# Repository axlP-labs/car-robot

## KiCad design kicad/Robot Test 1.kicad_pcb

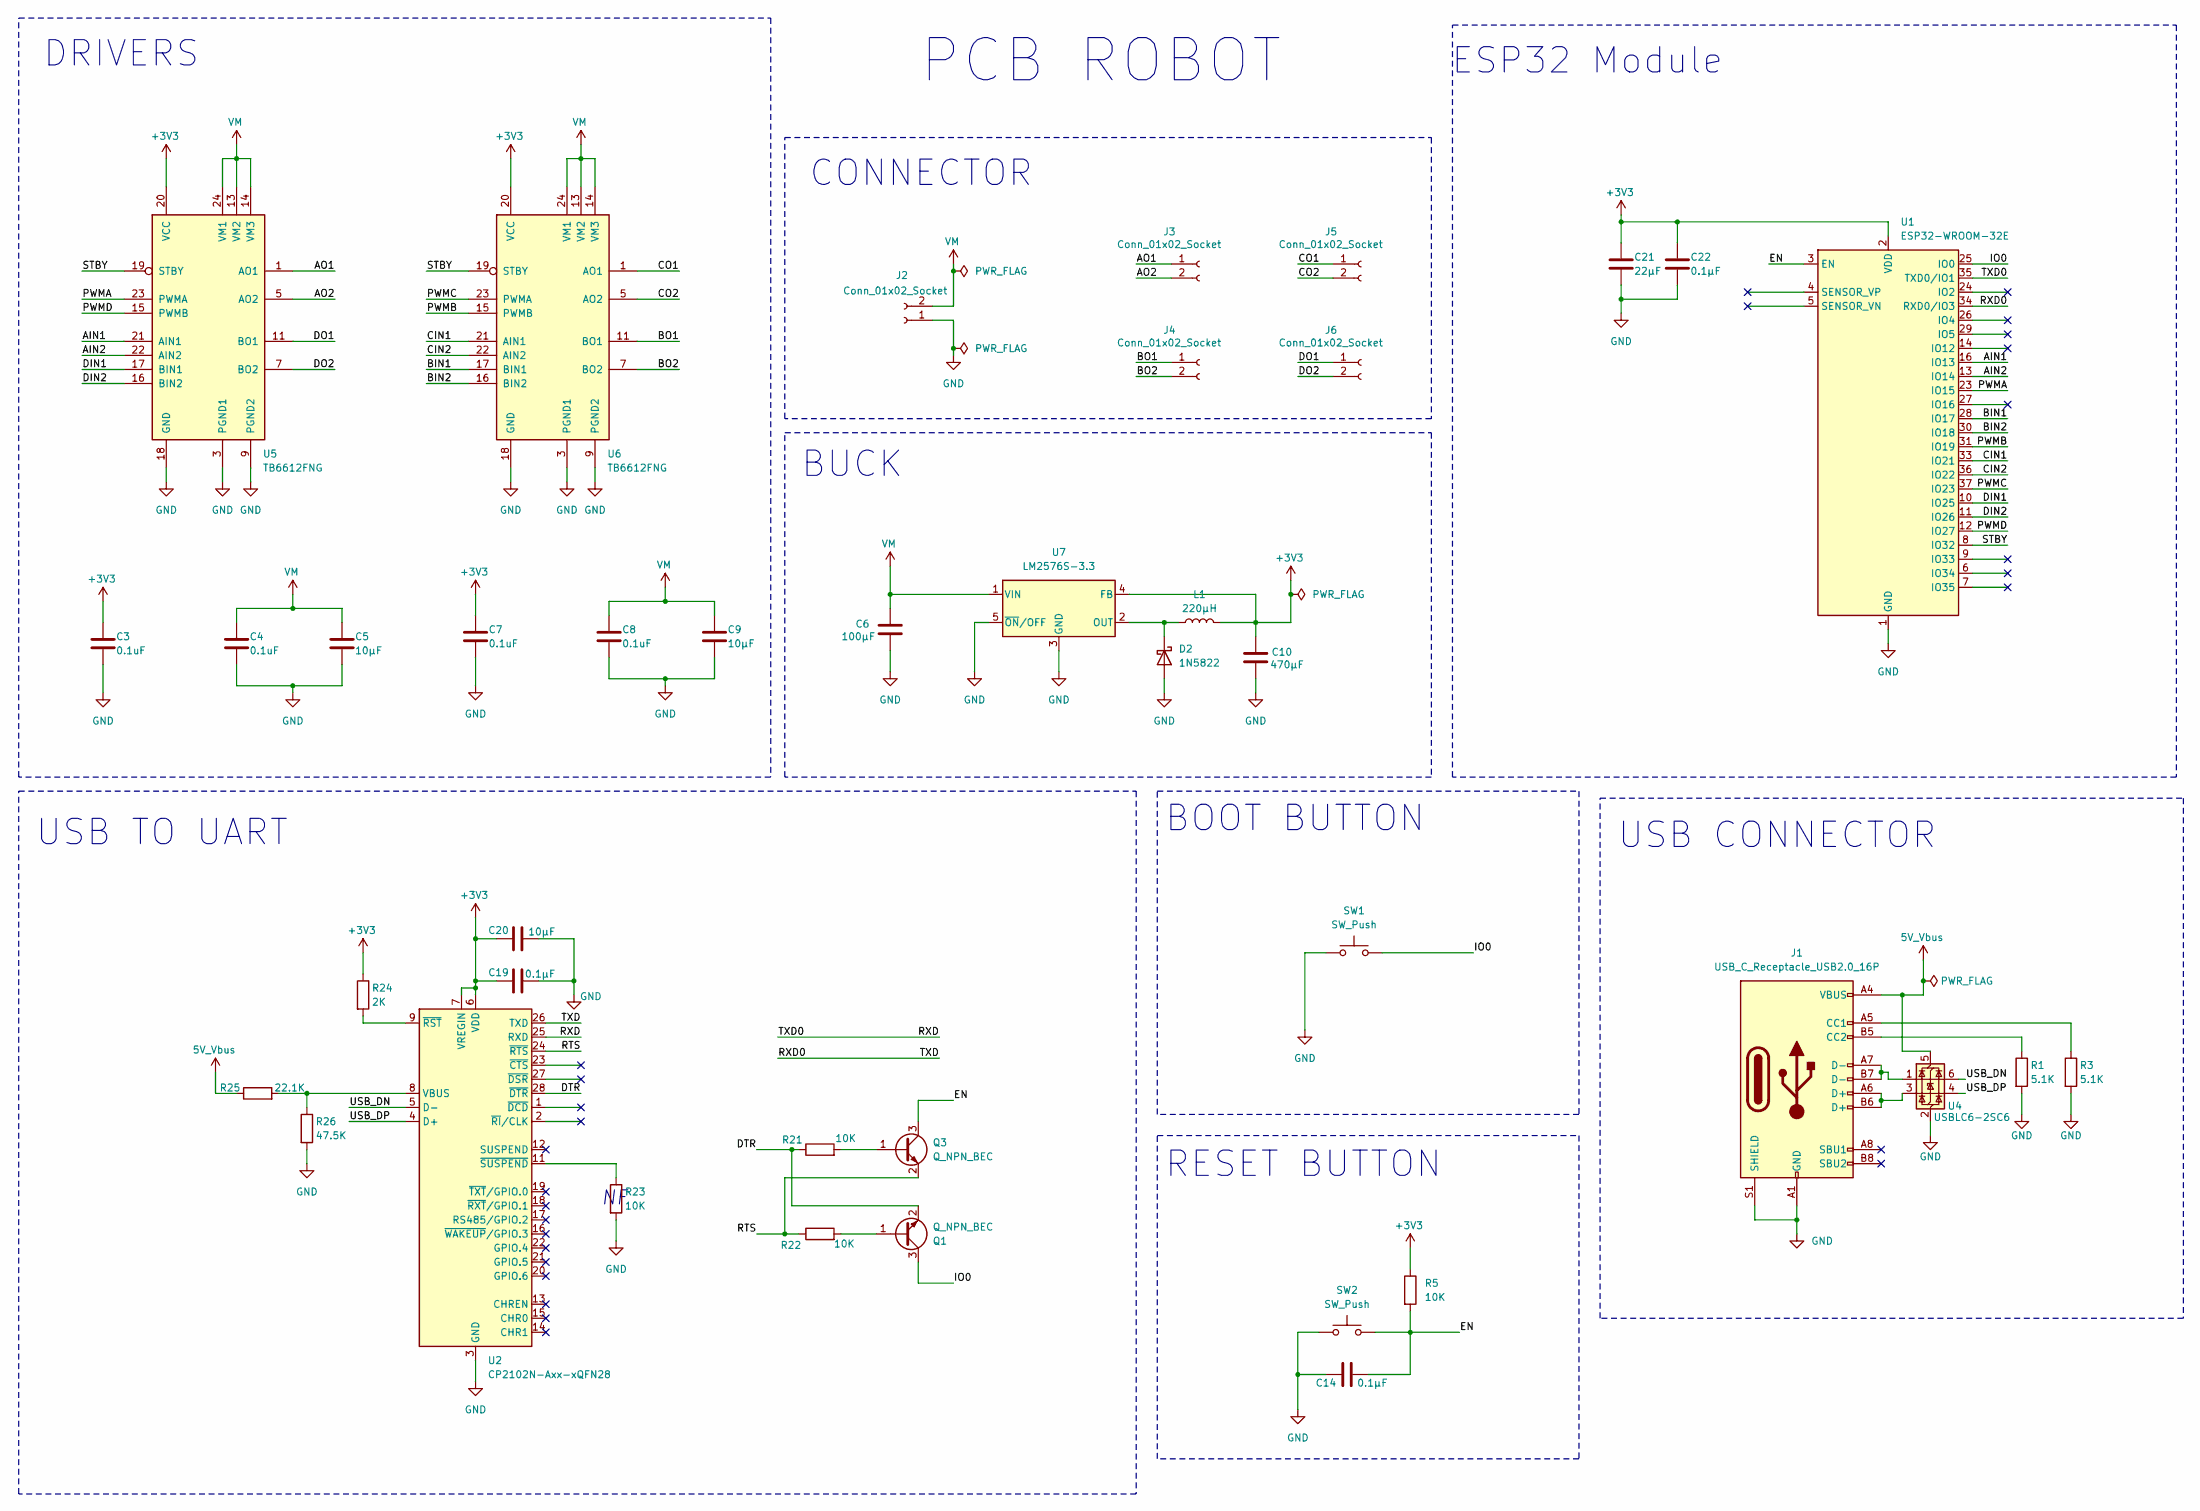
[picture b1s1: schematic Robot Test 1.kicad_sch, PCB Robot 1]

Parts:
C3, C4, C7, C8: 0.1uF; C_0805_2012Metric_Pad1.18x1.45mm_HandSolder
C5, C9, C20: 10µF; C_0805_2012Metric_Pad1.18x1.45mm_HandSolder
C6: 100µF; CP_Radial_D5.0mm_P2.00mm
C10: 470µF; CP_Radial_D10.0mm_P5.00mm
C14, C19, C22: 0.1µF; C_0805_2012Metric_Pad1.18x1.45mm_HandSolder
C21: 22µF; C_1206_3216Metric_Pad1.33x1.80mm_HandSolder
D2: 1N5822; D_DO-201AD_P15.24mm_Horizontal
J1: USB_C_Receptacle_USB2.0_16P; USB_C_Receptacle_JAE_DX07S016JA1R1500
J2, J3, J4, J5, J6: Conn_01x02_Socket; JST_XH_B2B-XH-A_1x02_P2.50mm_Vertical
L1: 220µH; L_Bourns_SRR1208_12.7x12.7mm
Q1, Q3: Q_NPN_BEC; SOT-23-3
R1, R3: 5.1K; R_1206_3216Metric_Pad1.30x1.75mm_HandSolder
R5, R21, R22, R23: 10K; R_1206_3216Metric_Pad1.30x1.75mm_HandSolder
R24: 2K; R_1206_3216Metric_Pad1.30x1.75mm_HandSolder
R25: 22.1K; R_1206_3216Metric_Pad1.30x1.75mm_HandSolder
R26: 47.5K; R_1206_3216Metric_Pad1.30x1.75mm_HandSolder
SW1, SW2: SW_Push; SW_SPST_Omron_B3FS-100xP
U1: ESP32-WROOM-32E
U2: CP2102N-Axx-xQFN28; QFN-28-1EP_5x5mm_P0.5mm_EP3.35x3.35mm
U4: USBLC6-2SC6; SOT-23-6
U5, U6: TB6612FNG; SSOP-24_5.3x8.2mm_P0.65mm
U7: LM2576S-3.3; TO-263-5_TabPin3

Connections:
5V_Vbus: J1.A4 (VBUS), J1.A9 (VBUS), J1.B4 (VBUS), J1.B9 (VBUS), R25.1, U4.5 (VBUS)
+3V3: C3.1, C7.1, C10.1, C19.1, C20.1, C21.1, C22.1, L1.2, R5.1, R24.1, U1.2 (VDD), U2.6 (VDD), U2.7 (VREGIN), U5.20 (VCC), U6.20 (VCC), U7.4 (FB)
/AIN1: U1.16 (IO13), U5.21 (AIN1)
/AIN2: U1.13 (IO14), U5.22 (AIN2)
/AO1: J3.1, U5.1 (AO1), U5.2 (AO1)
/AO2: J3.2, U5.5 (AO2), U5.6 (AO2)
/BIN1: U1.28 (IO17), U6.17 (BIN1)
/BIN2: U1.30 (IO18), U6.16 (BIN2)
/BO1: J4.1, U6.11 (BO1), U6.12 (BO1)
/BO2: J4.2, U6.7 (BO2), U6.8 (BO2)
/CIN1: U1.33 (IO21), U6.21 (AIN1)
/CIN2: U1.36 (IO22), U6.22 (AIN2)
/CO1: J5.1, U6.1 (AO1), U6.2 (AO1)
/CO2: J5.2, U6.5 (AO2), U6.6 (AO2)
/DIN1: U1.10 (IO25), U5.17 (BIN1)
/DIN2: U1.11 (IO26), U5.16 (BIN2)
/DO1: J6.1, U5.11 (BO1), U5.12 (BO1)
/DO2: J6.2, U5.7 (BO2), U5.8 (BO2)
/DTR: Q1.2 (E), R21.1, U2.28 (~DTR)
/EN: C14.2, Q3.3 (C), R5.2, SW2.2, U1.3 (EN)
/IO0: Q1.3 (C), SW1.2, U1.25 (IO0)
/PWMA: U1.23 (IO15), U5.23 (PWMA)
/PWMB: U1.31 (IO19), U6.15 (PWMB)
/PWMC: U1.37 (IO23), U6.23 (PWMA)
/PWMD: U1.12 (IO27), U5.15 (PWMB)
/RTS: Q3.2 (E), R22.1, U2.24 (~RTS)
/RXD: U1.35 (TXD0/IO1), U2.25 (RXD)
/RXD0: U1.34 (RXD0/IO3), U2.26 (TXD)
/STBY: U1.8 (IO32), U5.19 (STBY), U6.19 (STBY)
/USB_DN: U2.5 (D-), U4.6 (I/O1)
/USB_DP: U2.4 (D+), U4.4 (I/O2)
GND: C3.2, C4.2, C5.2, C6.2, C7.2, C8.2, C9.2, C10.2, C14.1, C19.2, C20.2, C21.2, C22.2, D2.2 (A), J1.A1 (GND), J1.A12 (GND), J1.B1 (GND), J1.B12 (GND), J1.S1 (SHIELD), J2.1, R1.2, R3.2, R23.2, R26.2, SW1.1, SW2.1, U1.1 (GND), U1.15 (GND), U1.38 (GND), U1.39 (GND), U2.3 (GND), U2.29 (GND), U4.2 (GND), U5.3 (PGND1), U5.4 (PGND1), U5.9 (PGND2), U5.10 (PGND2), U5.18 (GND), U6.3 (PGND1), U6.4 (PGND1), U6.9 (PGND2), U6.10 (PGND2), U6.18 (GND), U7.3 (GND), U7.5 (~ON/OFF)
unnamed: D2.1 (K), L1.1, U7.2 (OUT)
unnamed: J1.A5 (CC1), R3.1
unnamed: J1.B5 (CC2), R1.1
unnamed: J1.A6 (D+), J1.B6 (D+), U4.3 (I/O2)
unnamed: J1.A7 (D-), J1.B7 (D-), U4.1 (I/O1)
unnamed: Q1.1 (B), R22.2
unnamed: Q3.1 (B), R21.2
unnamed: R25.2, R26.1, U2.8 (VBUS)
unnamed: R24.2, U2.9 (~RST)
unnamed: R23.1, U2.11 (~SUSPEND)
VM: C4.1, C5.1, C6.1, C8.1, C9.1, J2.2, U5.13 (VM2), U5.14 (VM3), U5.24 (VM1), U6.13 (VM2), U6.14 (VM3), U6.24 (VM1), U7.1 (VIN)

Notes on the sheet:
RESET BUTTON
DRIVERS
CONNECTOR
PCB ROBOT
BOOT BUTTON
ESP32 Module
USB TO UART
USB CONNECTOR
BUCK

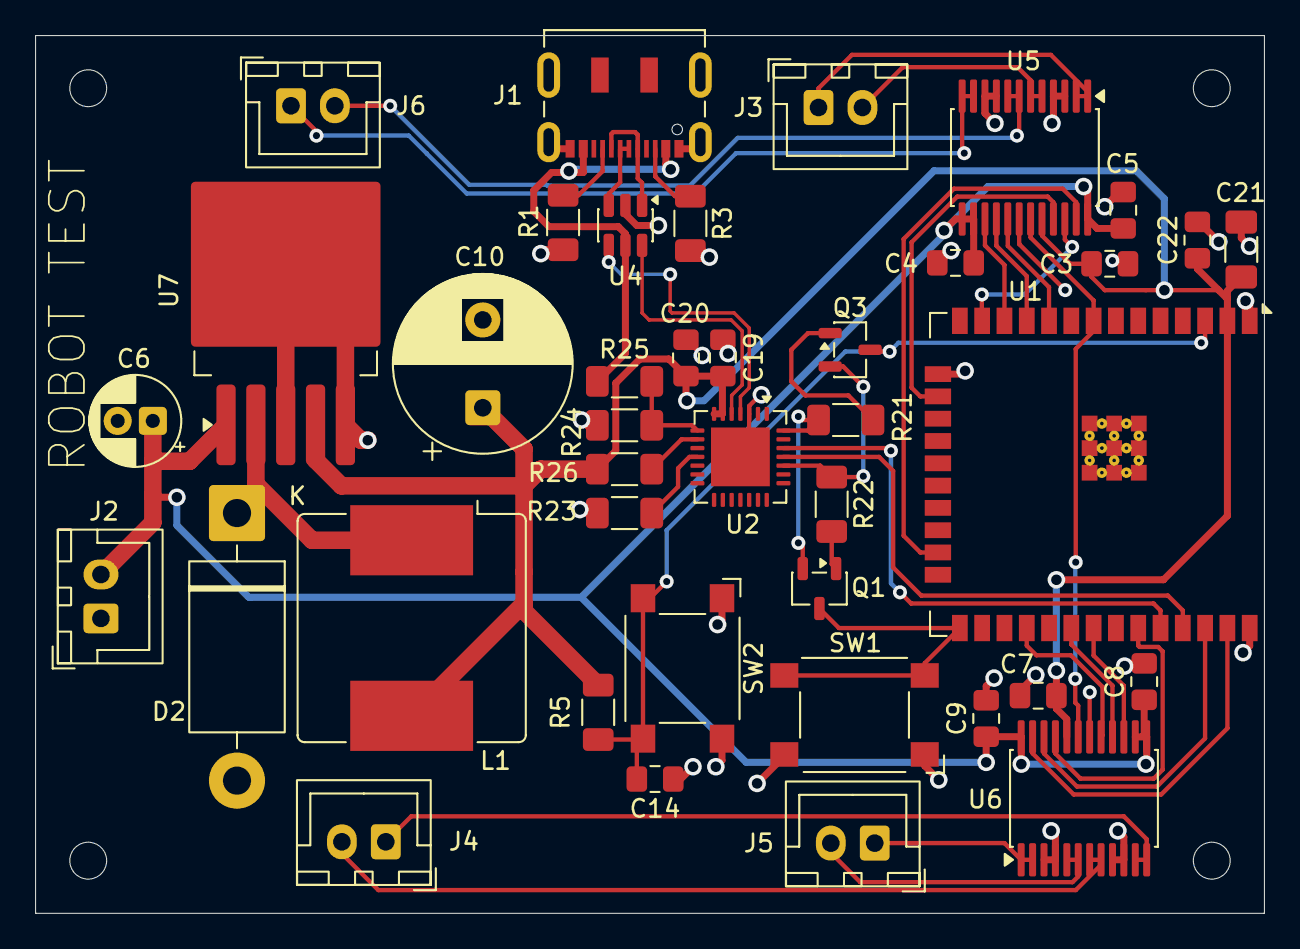
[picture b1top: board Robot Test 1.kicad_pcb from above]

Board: 2 copper layers, 70.0 x 50.0 mm, 40 parts (0 on the bottom side), 43 nets.
